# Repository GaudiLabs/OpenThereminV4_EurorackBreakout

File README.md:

# OpenThereminV4_EurorackBreakout
Break-Out-Modules for the OpenTheremin V45
Copyright (C) by GaudiLabs published under a public license.

OpenThereminV4 board design files:
https://github.com/GaudiLabs/OpenThereminV4

The Break-Out board uses the mocoLUFA firmware
Copyright (C) by morecat_lab
https://github.com/kuwatay/mocolufa

OpenTheremin V4 Eurorack Kits are available here:
https://gaudishop.ch/

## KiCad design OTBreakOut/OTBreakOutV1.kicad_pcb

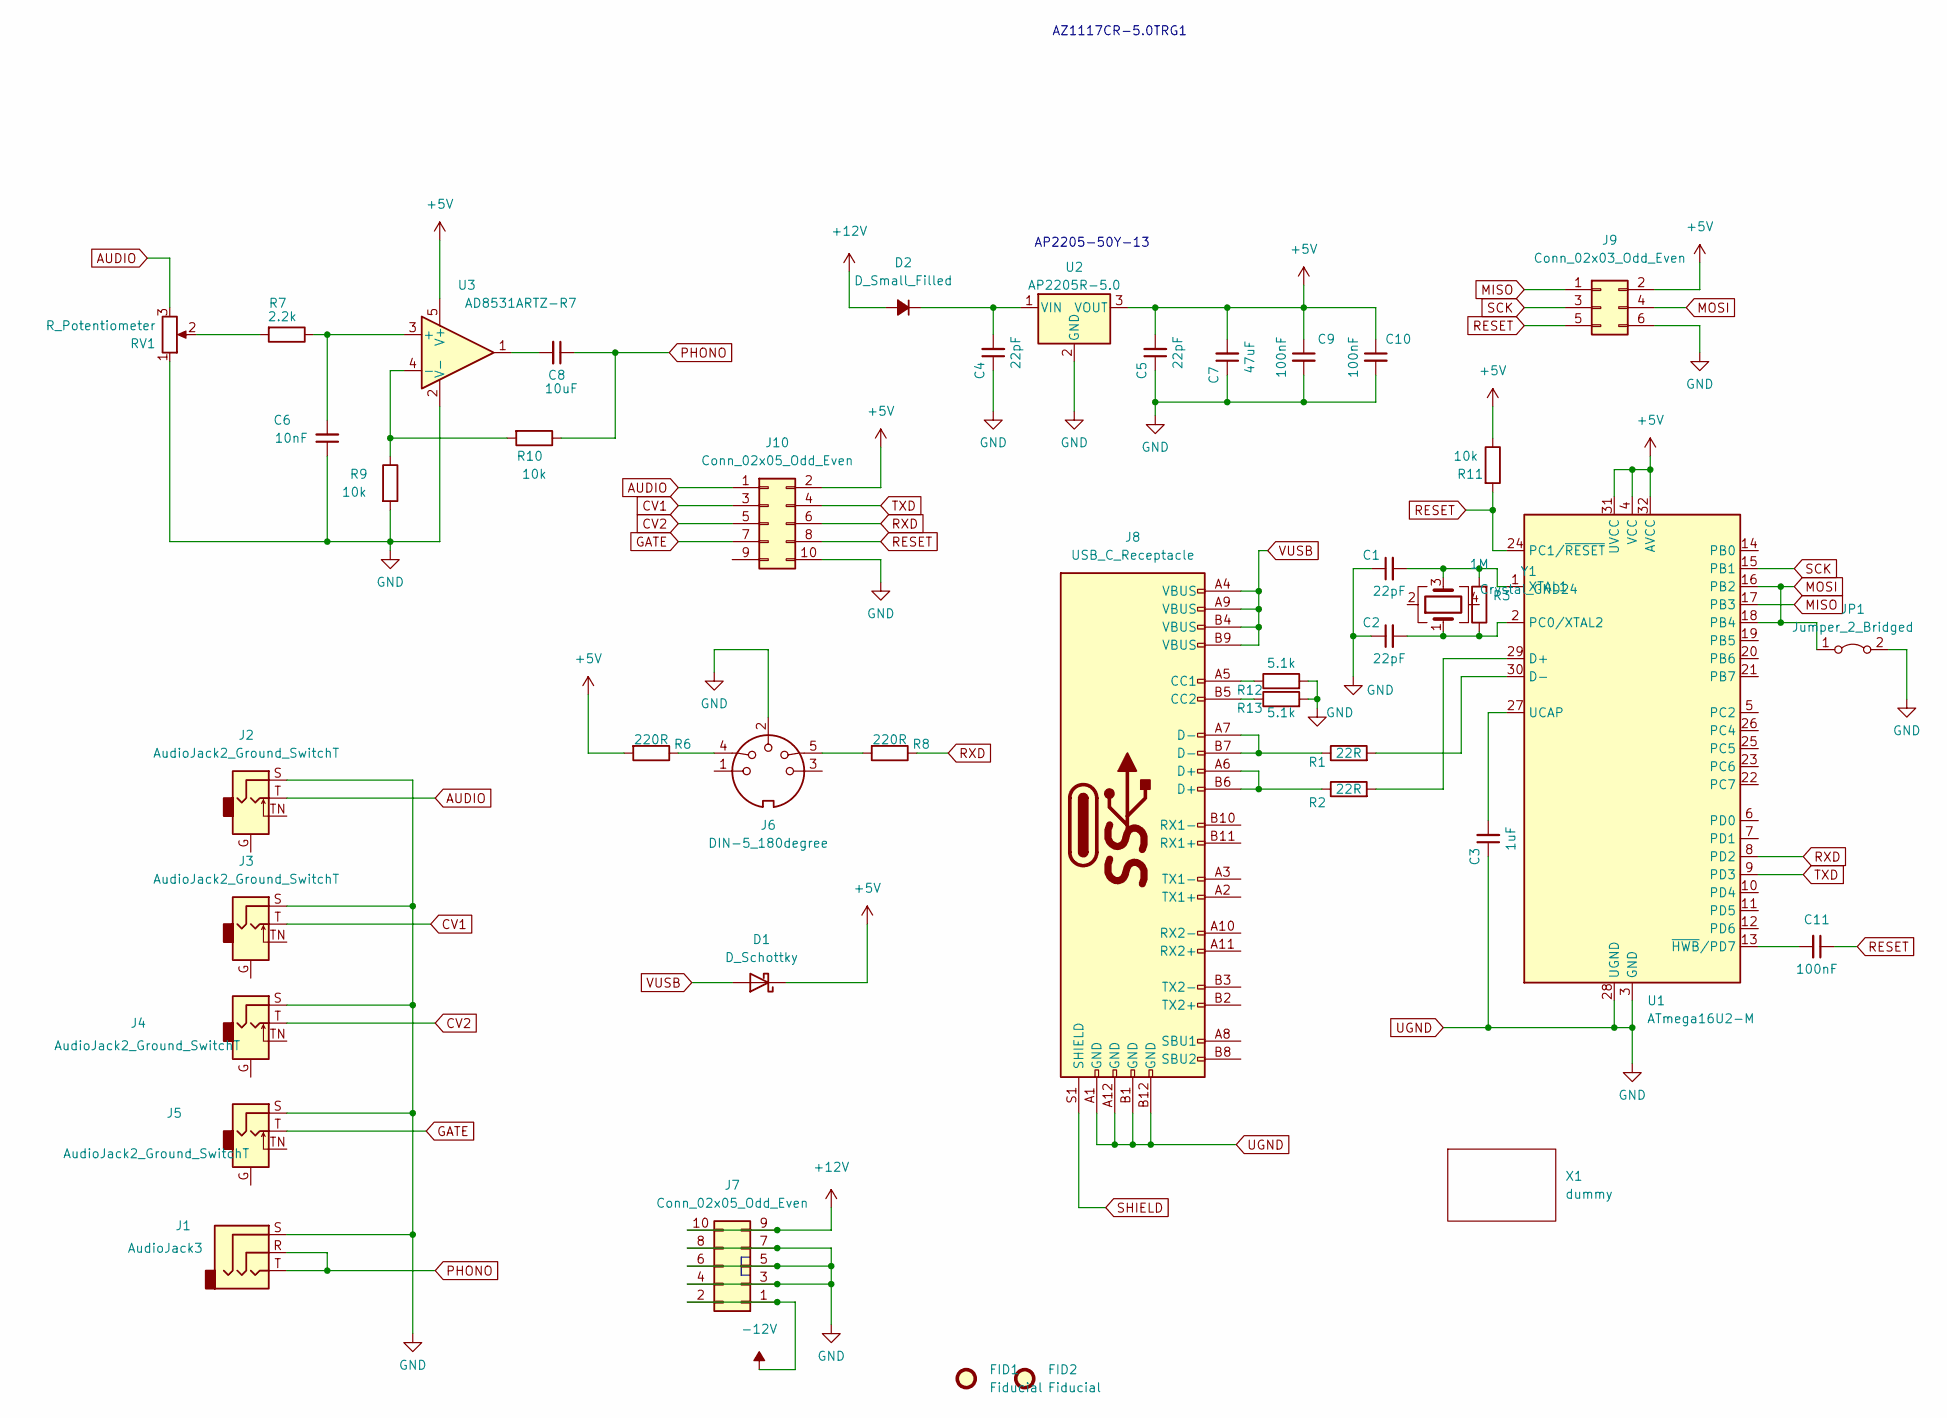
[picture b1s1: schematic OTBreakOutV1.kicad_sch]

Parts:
C1, C2, C4, C5: 22pF; C_0603_1608Metric
C3: 1uF; C_0603_1608Metric
C6: 10nF; C_0603_1608Metric
C7: 47uF; C_0805_2012Metric
C8: 10uF; C_0603_1608Metric
C9, C10, C11: 100nF; C_0603_1608Metric
D1: D_Schottky; D_SOD-123
D2: D_Small_Filled; D_SOD-123
FID1, FID2: Fiducial; Fiducial_1mm_Mask2mm
J1: AudioJack3; Jack_3.5mm_QingPu_WQP-PJ366ST_Vertical
J2, J3, J4, J5: AudioJack2_Ground_SwitchT; Jack_3.5mm_Stereo_WQP-PJ366ST_Vertical
J6: DIN-5_180degree; Deltron_691-0500
J7: Conn_02x05_Odd_Even; ModularConnector_10pin
J8: USB_C_Receptacle; UJ40_CVG_SMT_TR
J9: Conn_02x03_Odd_Even; Tag-Connect_TC2030-IDC-NL_2x03_P1.27mm_Vertical
J10: Conn_02x05_Odd_Even; OTBreakOut_2x05_P1.27mm_Vertical_SMD
JP1: Jumper_2_Bridged; SolderJumper-2_P1.3mm_Open_RoundedPad1.0x1.5mm
R1, R2: 22R; R_0603_1608Metric
R3: 1M; R_0603_1608Metric
R6, R8: 220R; R_0603_1608Metric
R7: 2.2k; R_0603_1608Metric
R9, R10, R11: 10k; R_0603_1608Metric
R12, R13: 5.1k; R_0603_1608Metric
RV1: R_Potentiometer; Alps_RK09K_Vertical
U1: ATmega16U2-M; QFN-32-1EP_5x5mm_P0.5mm_EP3.1x3.1mm
U2: AP2205R-5.0; SOT-89-3
U3: AD8531ARTZ-R7; SOT-23-5
X1: dummy; Smile
Y1: Crystal_GND24; Crystal_SMD_3225-4Pin_3.2x2.5mm

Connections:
+5V: C5.2, C7.2, C9.1, C10.1, D1.1 (K), J9.2, J10.2, R6.2, R11.1, U1.4 (VCC), U1.31 (UVCC), U1.32 (AVCC), U2.3 (VOUT), U3.5 (V+)
+12V: D2.2 (A), J7.9, J7.10
-12V: J7.1, J7.2
AUDIO: J2.T, J10.1, RV1.3
CV1: J3.T, J10.3
CV2: J4.T, J10.5
GATE: J5.T, J10.7
MISO: J9.1, U1.17 (PB3)
MOSI: J9.4, JP1.1 (A), U1.16 (PB2), U1.18 (PB4)
unnamed: C1.2, R3.2, U1.1 (XTAL1), Y1.3
unnamed: C2.2, R3.1, U1.2 (PC0/XTAL2), Y1.1
unnamed: C3.2, U1.27 (UCAP)
unnamed: C4.2, D2.1 (K), U2.1 (VIN)
unnamed: C6.2, R7.1, U3.3 (+)
unnamed: C8.2, U3.1
unnamed: J6.4, R6.1
unnamed: J6.5, R8.2
unnamed: J8.A5 (CC1), R12.1
unnamed: J8.A6 (D+), J8.B6 (D+), R2.1
unnamed: J8.A7 (D-), J8.B7 (D-), R1.1
unnamed: J8.B5 (CC2), R13.1
unnamed: R1.2, U1.30 (D-)
unnamed: R2.2, U1.29 (D+)
unnamed: R7.2, RV1.2
unnamed: R9.1, R10.2, U3.4 (-)
unnamed: C11.2, U1.13 (~HWB/PD7)
PHONO: C8.1, J1.R, J1.T, R10.1
RESET: C11.1, J9.5, J10.8, R11.2, U1.24 (PC1/~RESET)
RXD: J10.6, R8.1, U1.8 (PD2)
SCK: J9.3, U1.15 (PB1)
TXD: J10.4, U1.9 (PD3)
UGND: C1.1, C2.1, C3.1, C4.1, C5.1, C6.1, C7.1, C9.2, C10.2, J1.S, J2.S, J3.S, J4.S, J5.S, J6.2, J7.3, J7.4, J7.5, J7.6, J7.7, J7.8, J8.A1 (GND), J8.A12 (GND), J8.B1 (GND), J8.B12 (GND), J9.6, J10.10, JP1.2 (B), R9.2, R12.2, R13.2, RV1.1, U1.3 (GND), U1.28 (UGND), U1.33 (GND), U2.2 (GND), U3.2 (V-)
VUSB: D1.2 (A), J8.A4 (VBUS), J8.A9 (VBUS), J8.B4 (VBUS), J8.B9 (VBUS)

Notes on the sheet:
AZ1117CR-5.0TRG1
AP2205-50Y-13

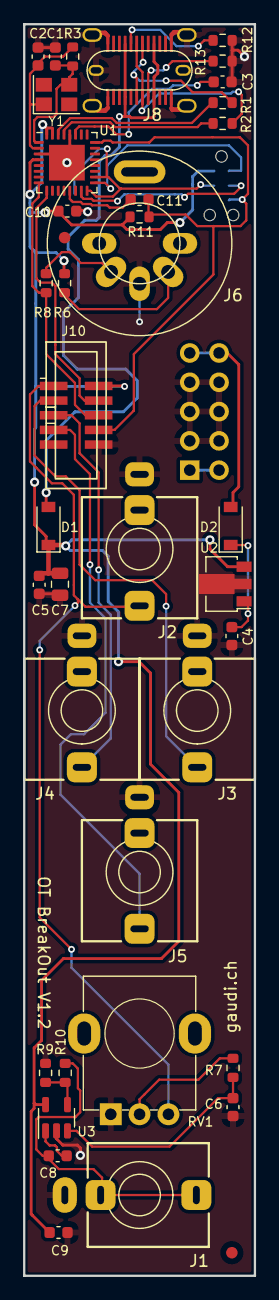
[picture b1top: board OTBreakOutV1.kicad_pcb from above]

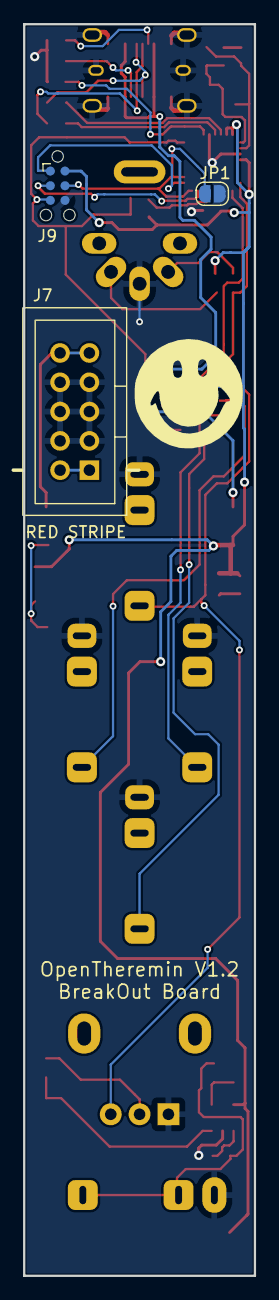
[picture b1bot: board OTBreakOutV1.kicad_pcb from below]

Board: 2 copper layers, 20.0 x 108.5 mm, 43 parts (4 on the bottom side), 33 nets.
